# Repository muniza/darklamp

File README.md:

darklamp
========

Dark Rainbow Lamp
Details can be found on the wiki:
https://github.com/muniza/darklamp/wiki/

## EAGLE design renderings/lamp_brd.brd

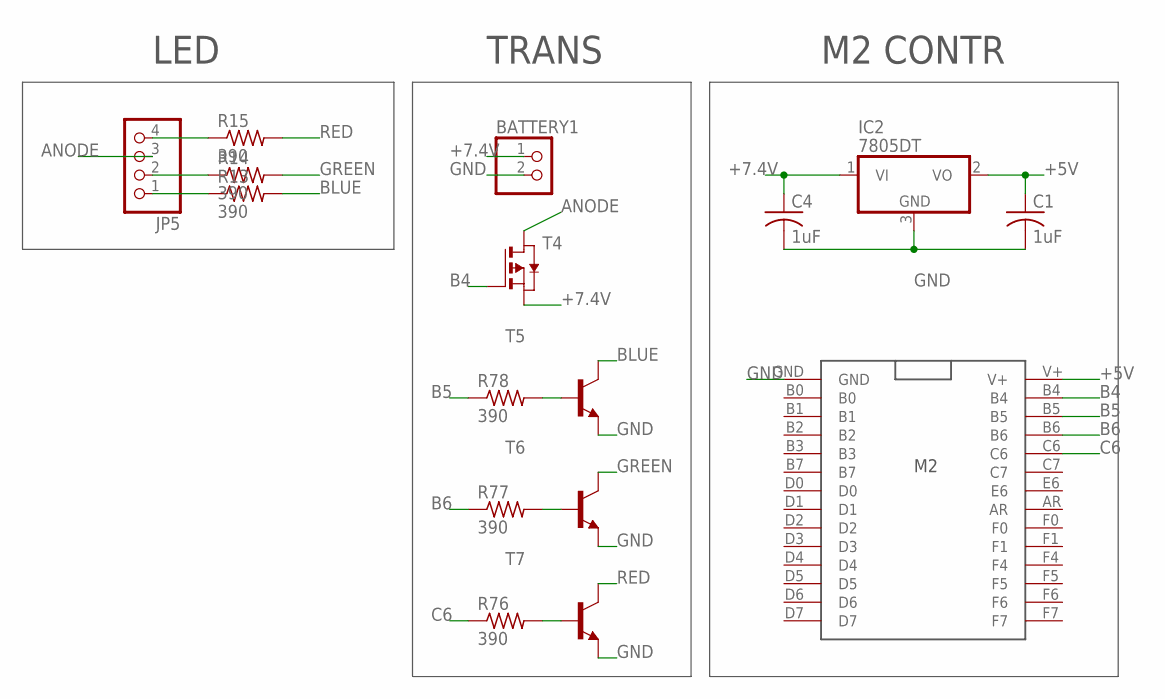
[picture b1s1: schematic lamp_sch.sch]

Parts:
BATTERY1: PINHD-1X2; 1X02
C1, C4: 1uF; C0603
IC2: 7805DT; TO252
JP5: PINHD-1X4; 1X04
R13, R14, R15, R76, R77, R78: 390; R0603
T4: PMOSSOT23; SOT-23
T5, T6, T7: MMBT3904LT1-NPN-SOT23-BEC; SOT23-BEC
U$2: M2

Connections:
+5V: C1.1, IC2.2 (VO), U$2.V+
+7.4V: BATTERY1.1, C4.1, IC2.1 (VI), T4.2 (S)
ANODE: JP5.3, T4.1 (D)
B4: T4.3 (G), U$2.B4
B5: R78.1, U$2.B5
B6: R77.1, U$2.B6
BLUE: R13.2, T5.C
C6: R76.1, U$2.C6
GND: BATTERY1.2, C1.2, C4.2, IC2.3 (GND), T5.E, T6.E, T7.E, U$2.GND
GREEN: R14.2, T6.C
unnamed: JP5.4, R15.1
unnamed: JP5.2, R14.1
unnamed: JP5.1, R13.1
unnamed: R76.2, T7.B
unnamed: R77.2, T6.B
unnamed: R78.2, T5.B
RED: R15.2, T7.C

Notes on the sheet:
LED
TRANS
M2 CONTR

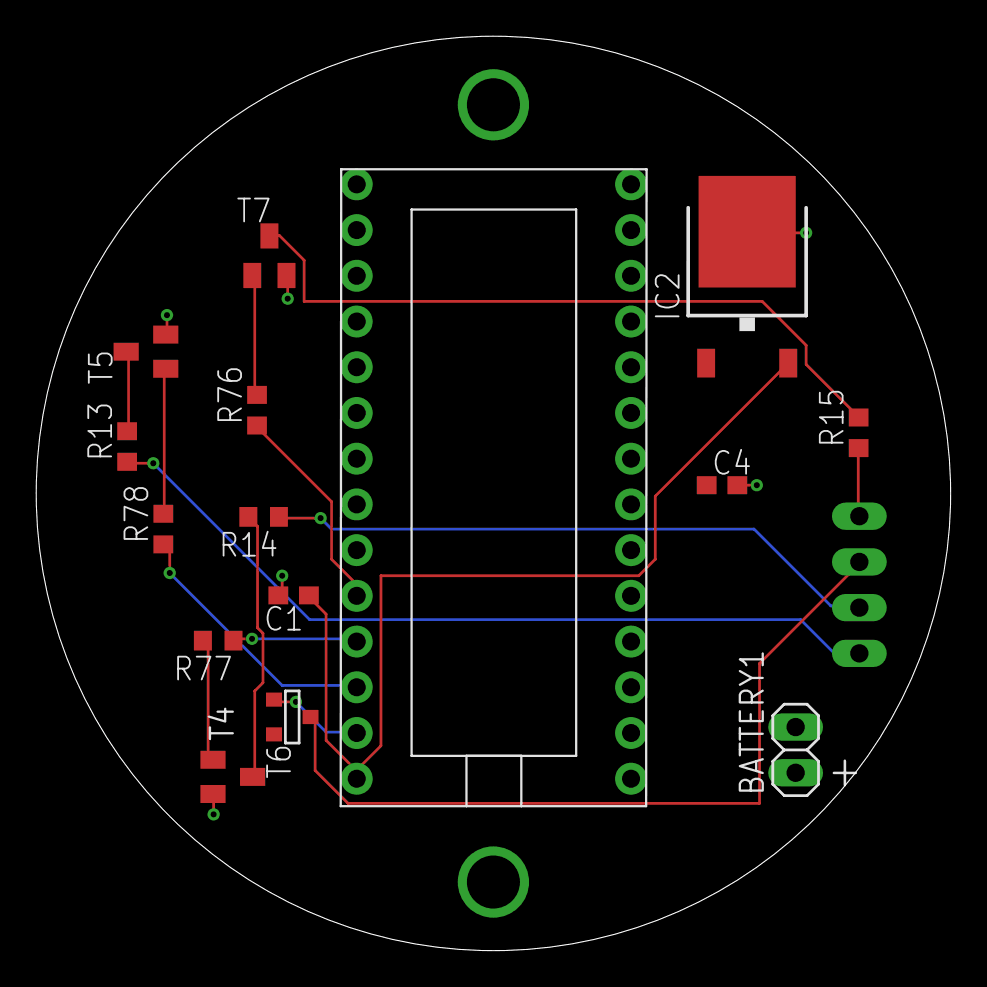
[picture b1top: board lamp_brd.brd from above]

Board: 2 copper layers, 50.8 x 50.8 mm, 16 parts (1 on the bottom side), 17 nets.

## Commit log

2014-12-18 added system overview
2014-12-18 Added code and bom
2014-12-18 added schematic
2014-12-18 quick change to code for timing
2014-12-18 added pictures of final product
2014-12-18 Added mechanical
2014-12-18 Added renderings
2014-12-19 added schematic and board files for the pcb
